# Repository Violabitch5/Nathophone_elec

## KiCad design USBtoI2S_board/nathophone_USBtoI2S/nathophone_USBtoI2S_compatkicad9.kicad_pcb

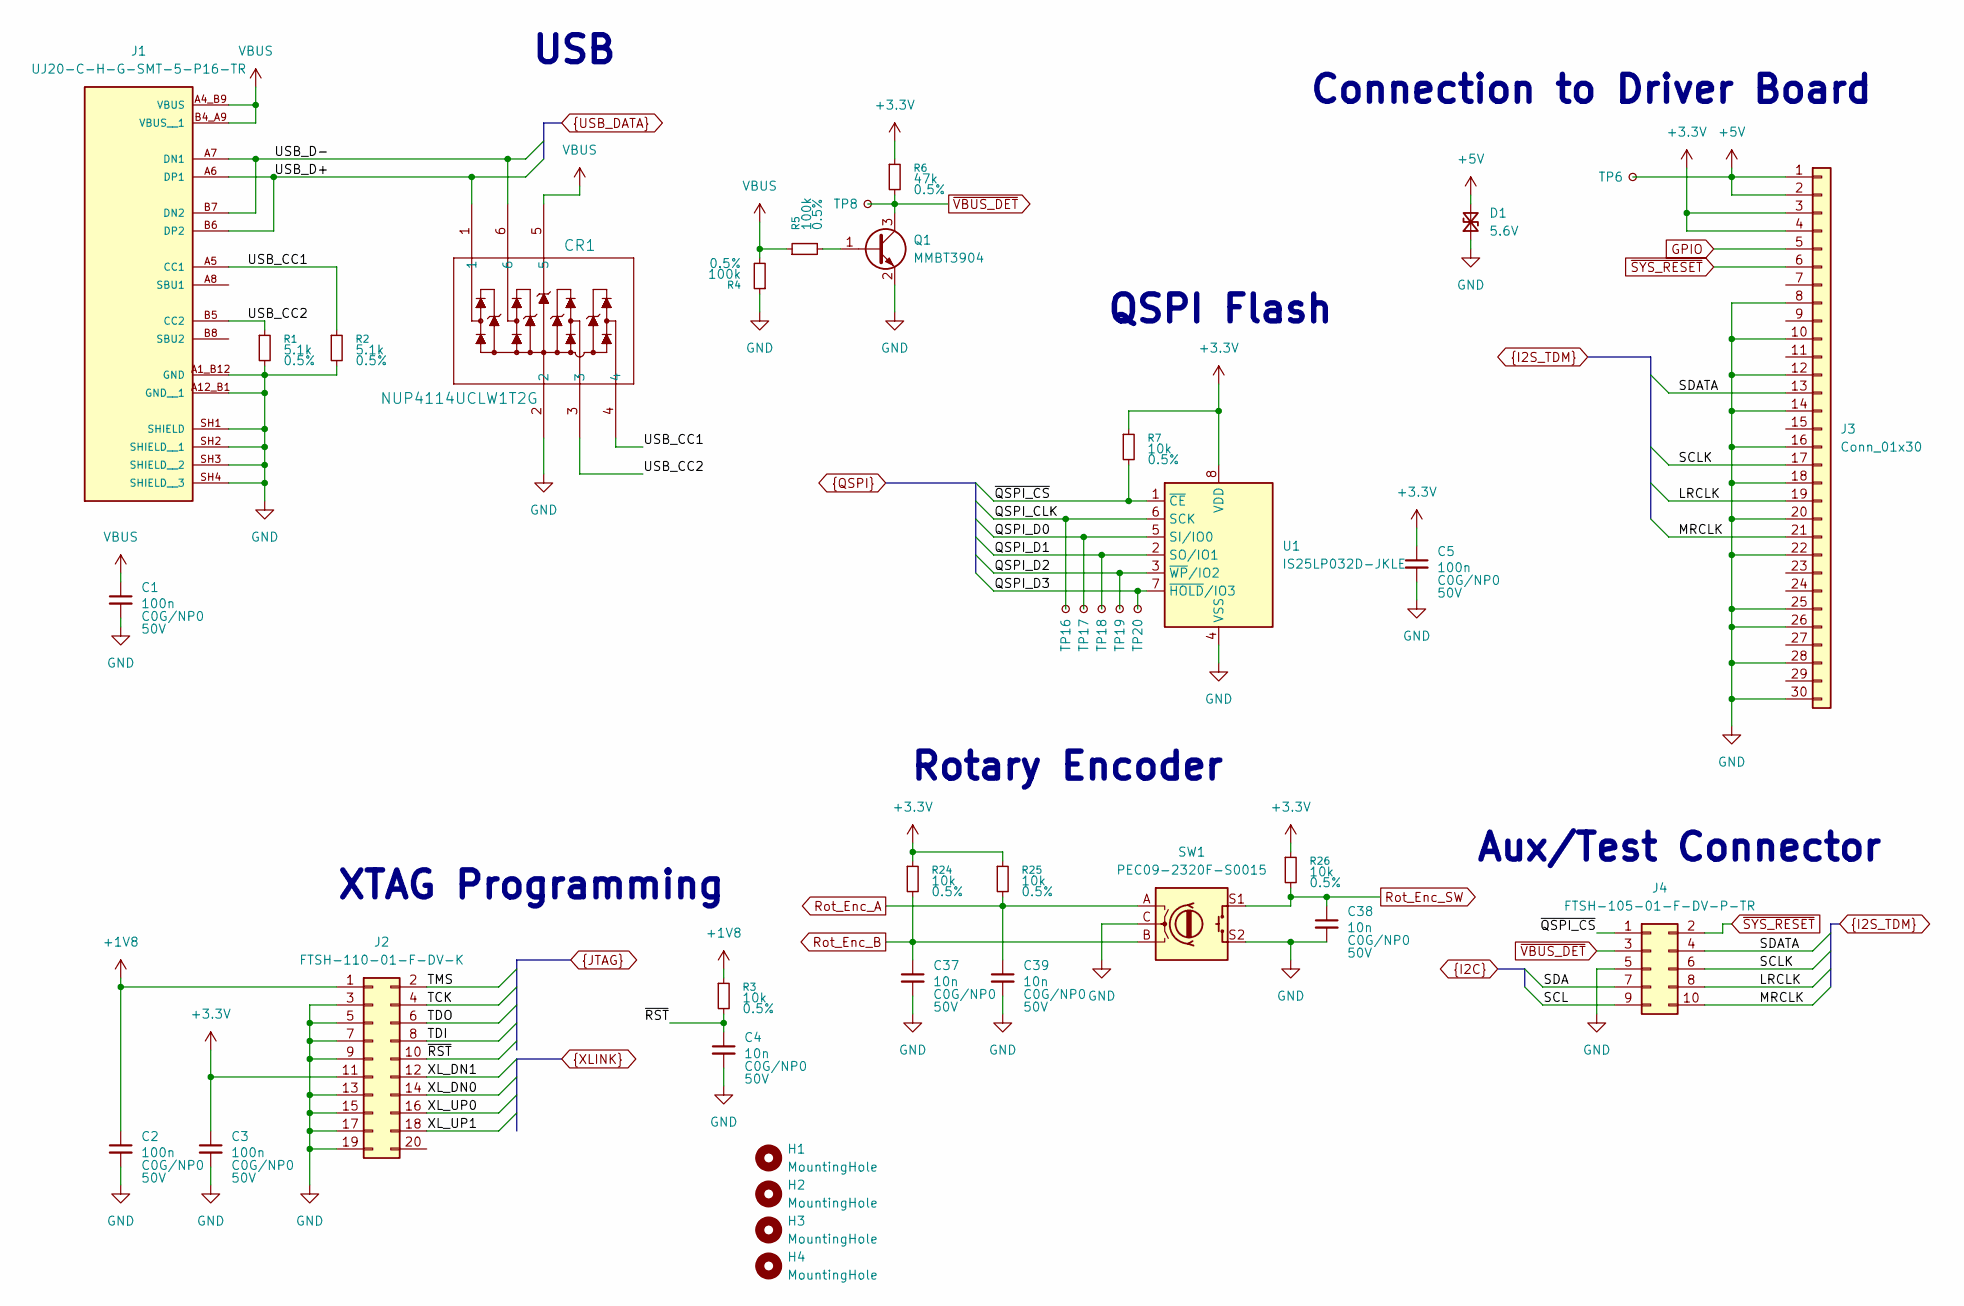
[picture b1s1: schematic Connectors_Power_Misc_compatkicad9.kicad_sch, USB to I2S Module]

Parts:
C1, C2, C3, C5: 100n; CAPC1810X65N; Voltage Rating 50V; MPN GRMJN65C1H104JE01D; DigiKey Part Number 490-GRMJN65C1H104JE01DCT-ND
C4, C37, C38, C39: 10n; C_0805_2012Metric_Pad1.18x1.45mm_HandSolder; Voltage Rating 50V; MPN GRM2195C1H103JA01D; DigiKey Part Number 490-1642-1-ND
CR1: NUP4114UCLW1T2G; SOT-363_SC-70-6; MPN NUP4114UCLW1T2G; DigiKey Part Number NUP4114UCLW1T2GOSCT-ND
D1: 5.6V; SOD-962_SL2_TOS; MPN DF2B6M4BSL,L3F; DigiKey Part Number 264-DF2B6M4BSL,L3FCT-ND
H1, H2, H3, H4: MountingHole; MountingHole_2.7mm_M2.5_DIN965
J1: UJ20-C-H-G-SMT-5-P16-TR; SAMESKY_UJ20-C-H-G-SMT-5-P16-TR; PARTREV 1.01; DigiKey Part Number 2223-UJ20-C-H-G-SMT-5-P16-TRCT-ND
J2: FTSH-110-01-F-DV-K; CON20_2X10_DUK_FTSH_SAI-M; MPN FTSH-110-01-F-DV-K; DigiKey Part Number SAM8802-ND
J3: Conn_01x30; CON_525593072_MOL; MPN 0525593072; DigiKey Part Number 900-0525593072TR-ND
J4: FTSH-105-01-F-DV-P-TR; PinHeader_2x05_P1.27mm_Vertical_SMD; MPN FTSH-105-01-F-DV-P-TR; DigiKey Part Number SAM13161CT-ND
Q1: MMBT3904; SOT-23; MPN MMBT3904; DigiKey Part Number 4530-MMBT3904CT-ND
R1, R2: 5.1k; R_0805_2012Metric_Pad1.20x1.40mm_HandSolder; MPN RNCF0805DTE5K10; DigiKey Part Number 738-RNCF0805DTE5K10CT-ND
R3, R7, R24, R25, R26: 10k; R_0805_2012Metric_Pad1.20x1.40mm_HandSolder; MPN RNCF0805DTE10K0; DigiKey Part Number RNCF0805DTE10K0CT-ND
R4, R5: 100k; R_0805_2012Metric_Pad1.20x1.40mm_HandSolder; MPN RNCF0805DTE100K; DigiKey Part Number 738-RNCF0805DTE100KCT-ND
R6: 47k; R_0805_2012Metric_Pad1.20x1.40mm_HandSolder; MPN RNCF0805DTE47K0; DigiKey Part Number 738-RNCF0805DTE47K0CT-ND
SW1: PEC09-2320F-S0015; RotaryEncoder_Bourns_Horizontal_PEC09-2xxxF-Sxxxx; MPN PEC09-2320F-S0015; DigiKey Part Number PEC09-2320F-S0015-ND
TP6, TP8, TP16, TP17, TP18, TP19, TP20: TestPoint_Small; TestPoint_Pad_D1.5mm
U1: IS25LP032D-JKLE; WSON-8-1EP_6x5mm_P1.27mm_EP3.4x4mm; MPN IS25LP032D-JKLE-TR; DigiKey Part Number 706-IS25LP032D-JKLE-TRCT-ND

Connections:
+1V8: C2.1, J2.1, R3.1; also elsewhere on the board
+3.3V: C3.1, C5.1, J2.11, J3.3, J3.4, R6.1, R7.1, R24.1, R25.1, R26.1, U1.8 (VDD); also elsewhere on the board
+5V: D1.2 (A2), J3.1, J3.2, TP6.1 (1_1); also elsewhere on the board
/Connectors_Misc/USB_CC1: CR1.4, J1.A5 (CC1), R2.1
/Connectors_Misc/USB_CC2: CR1.3, J1.B5 (CC2), R1.1
GND: C1.2, C2.2, C3.2, C4.2, C5.2, C37.2, C38.2, C39.2, CR1.2, D1.1 (A1), J1.A1_B12 (GND), J1.A12_B1 (GND__1), J1.SH1 (SHIELD), J1.SH2 (SHIELD__1), J1.SH3 (SHIELD__2), J1.SH4 (SHIELD__3), J2.3, J2.5, J2.7, J2.9, J2.13, J2.15, J2.17, J2.19, J3.8, J3.10, J3.12, J3.14, J3.16, J3.18, J3.20, J3.22, J3.25, J3.26, J3.28, J3.30, J4.5, Q1.2 (E), R1.2, R2.2, R4.1, SW1.C, SW1.S2, U1.4 (VSS); also elsewhere on the board
GPIO: J3.5; also elsewhere on the board
LRCLK: J3.19, J4.8; also elsewhere on the board
MRCLK: J3.21, J4.10; also elsewhere on the board
unnamed: Q1.1 (B), R5.2
QSPI_CLK: TP16.1 (1_1), U1.6 (SCK); also elsewhere on the board
QSPI_D0: TP17.1 (1_1), U1.5 (SI/IO0); also elsewhere on the board
QSPI_D1: TP18.1 (1_1), U1.2 (SO/IO1); also elsewhere on the board
QSPI_D2: TP19.1 (1_1), U1.3 (~WP/IO2); also elsewhere on the board
QSPI_D3: TP20.1 (1_1), U1.7 (~HOLD/IO3); also elsewhere on the board
Rot_Enc_A: C39.1, R25.2, SW1.A; also elsewhere on the board
Rot_Enc_B: C37.1, R24.2, SW1.B; also elsewhere on the board
Rot_Enc_SW: C38.1, R26.2, SW1.S1; also elsewhere on the board
SCL: J4.9; also elsewhere on the board
SCLK: J3.17, J4.6; also elsewhere on the board
SDA: J4.7; also elsewhere on the board
SDATA: J3.13, J4.4; also elsewhere on the board
TCK: J2.4; also elsewhere on the board
TDI: J2.8; also elsewhere on the board
TDO: J2.6; also elsewhere on the board
TMS: J2.2; also elsewhere on the board
USB_D+: CR1.1, J1.A6 (DP1), J1.B6 (DP2); also elsewhere on the board
USB_D-: CR1.6, J1.A7 (DN1), J1.B7 (DN2); also elsewhere on the board
VBUS: C1.1, CR1.5, J1.A4_B9 (VBUS), J1.B4_A9 (VBUS__1), R4.2, R5.1
XL_DN0: J2.14; also elsewhere on the board
XL_DN1: J2.12; also elsewhere on the board
XL_UP0: J2.16; also elsewhere on the board
XL_UP1: J2.18; also elsewhere on the board
~QSPI_CS: J4.1, R7.2, U1.1 (~CE); also elsewhere on the board
~RST: C4.1, J2.10, R3.2; also elsewhere on the board
~SYS_RESET: J3.6, J4.2; also elsewhere on the board
~VBUS_DET: J4.3, Q1.3 (C), R6.2, TP8.1 (1_1); also elsewhere on the board

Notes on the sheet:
Connection to Driver Board
Rotary Encoder
USB
QSPI Flash
XTAG Programming
Aux/Test Connector

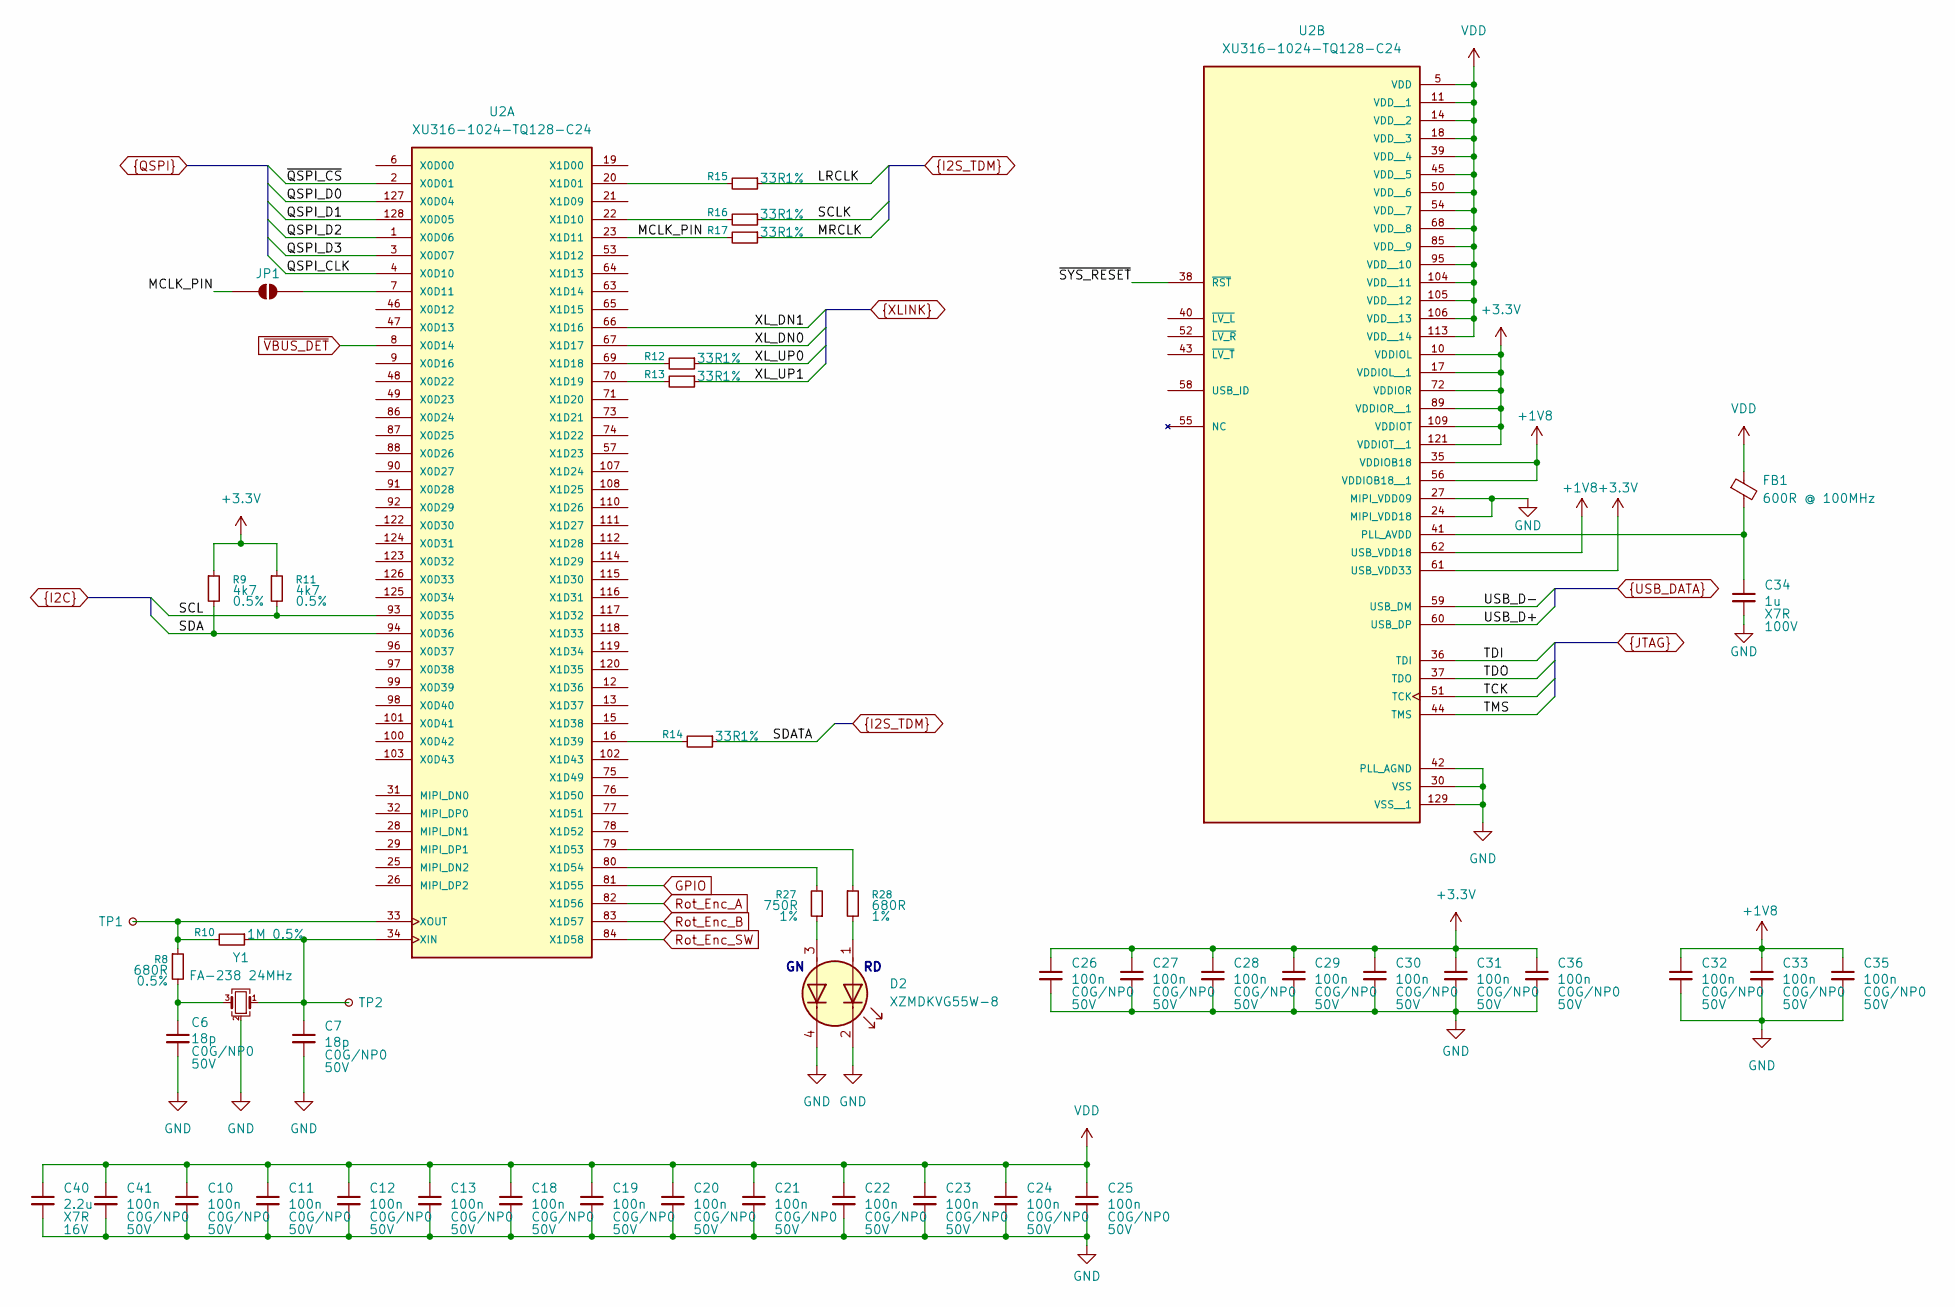
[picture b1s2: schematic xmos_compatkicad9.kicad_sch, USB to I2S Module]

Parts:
C6, C7: 18p; C_0603_1608Metric; Voltage Rating 50V; MPN C0603C180C5GACTU; DigiKey Part Number 399-C0603C180C5GACTUCT-ND
C10, C11, C12, C13, C18, C19, C20, C21, C22, C23, C24, C25, C26, C27, C28, C29, C30, C31, C32, C33, C35, C36, C41: 100n; CAPC1810X65N; Voltage Rating 50V; MPN GRMJN65C1H104JE01D; DigiKey Part Number 490-GRMJN65C1H104JE01DCT-ND
C34: 1u; C_0603_1608Metric; Voltage Rating 100V; MPN C1608X7R2A105K080AC; DigiKey Part Number 445-C1608X7R2A105K080ACCT-ND
C40: 2.2u; C_0805_2012Metric_Pad1.18x1.45mm_HandSolder; Voltage Rating 16V; MPN C2012X7R1C225K125AB; DigiKey Part Number 445-1420-1-ND
D2: XZMDKVG55W-8; LED_XZMDKVG55W-8; MPN XZMDKVG55W-8; DigiKey Part Number 1497-1183-1-ND
FB1: 600R @ 100MHz; C_0805_2012Metric_Pad1.18x1.45mm_HandSolder; MPN HZ0805E601R-10; DigiKey Part Number 240-2399-1-ND
JP1: SolderJumper_2_Open; SolderJumper-2_P1.3mm_Open_RoundedPad1.0x1.5mm
R8: 680R; R_0603_1608Metric; MPN RT0603DRD07680RL; DigiKey Part Number 311-680DCT-ND
R9, R11: 4k7; R_0805_2012Metric_Pad1.20x1.40mm_HandSolder; MPN RNCF0805DTE4K70; DigiKey Part Number 738-RNCF0805DTE4K70CT-ND
R10: 1M; R_0603_1608Metric; MPN RC0603DR-071ML; DigiKey Part Number 13-RC0603DR-071MLCT-ND
R12, R13, R14, R15, R16, R17: 33R; R_0805_2012Metric_Pad1.20x1.40mm_HandSolder; MPN RC0805FR-0733RL; DigiKey Part Number 311-33.0CRCT-ND
R27: 750R; R_0805_2012Metric_Pad1.20x1.40mm_HandSolder; MPN CRCW0805750RFKEA; DigiKey Part Number 541-750CCT-ND
R28: 680R; R_0805_2012Metric_Pad1.20x1.40mm_HandSolder; MPN CRCW0805680RFKEA; DigiKey Part Number 541-680CCT-ND
TP1, TP2: TestPoint_Small; TestPoint_Pad_D1.5mm
U2: XU316-1024-TQ128-C24; QFP40P1600X1600X120-129N; PARTREV 2025/1/13; DigiKey Part Number 880-XU316-1024-TQ128-C24-ND
Y1: FA-238 24MHz; Crystal_SMD_3225-4Pin_3.2x2.5mm; MPN FA-238 24.0000MB-C3; DigiKey Part Number SER3689CT-ND

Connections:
+1V8: C32.1, C33.1, C35.1, U2.35 (VDDIOB18), U2.56 (VDDIOB18__1), U2.62 (USB_VDD18); also elsewhere on the board
+3.3V: C26.1, C27.1, C28.1, C29.1, C30.1, C31.1, C36.1, R9.1, R11.1, U2.10 (VDDIOL), U2.17 (VDDIOL__1), U2.61 (USB_VDD33), U2.72 (VDDIOR), U2.89 (VDDIOR__1), U2.109 (VDDIOT), U2.121 (VDDIOT__1); also elsewhere on the board
/XMOS/MCLK_PIN: JP1.2 (B), R17.2, U2.23 (X1D11)
/XMOS/~SYS_RESET: U2.38 (~RST)
GND: C6.2, C7.2, C10.2, C11.2, C12.2, C13.2, C18.2, C19.2, C20.2, C21.2, C22.2, C23.2, C24.2, C25.2, C26.2, C27.2, C28.2, C29.2, C30.2, C31.2, C32.2, C33.2, C34.2, C35.2, C36.2, C40.2, C41.2, D2.2 (K1), D2.4 (K2), U2.24 (MIPI_VDD18), U2.27 (MIPI_VDD09), U2.30 (VSS), U2.42 (PLL_AGND), U2.129 (VSS__1), Y1.2 (G), Y1.4 (G); also elsewhere on the board
GPIO: U2.81 (X1D55); also elsewhere on the board
LRCLK: R15.1; also elsewhere on the board
MRCLK: R17.1; also elsewhere on the board
unnamed: C6.1, R8.2, Y1.3
unnamed: D2.1 (A1), R28.2
unnamed: D2.3 (A2), R27.1
unnamed: JP1.1 (A), U2.7 (X0D11)
unnamed: R15.2, U2.20 (X1D01)
unnamed: R16.2, U2.22 (X1D10)
unnamed: R12.2, U2.69 (X1D18)
unnamed: R13.2, U2.70 (X1D19)
unnamed: R14.2, U2.16 (X1D39)
unnamed: R28.1, U2.79 (X1D53)
unnamed: R27.2, U2.80 (X1D54)
unnamed: C7.1, R10.1, TP2.1 (1_1), U2.34 (XIN), Y1.1
unnamed: R8.1, R10.2, TP1.1 (1_1), U2.33 (XOUT)
unnamed: C34.1, FB1.2, U2.41 (PLL_AVDD)
QSPI_CLK: U2.4 (X0D10); also elsewhere on the board
QSPI_D0: U2.127 (X0D04); also elsewhere on the board
QSPI_D1: U2.128 (X0D05); also elsewhere on the board
QSPI_D2: U2.1 (X0D06); also elsewhere on the board
QSPI_D3: U2.3 (X0D07); also elsewhere on the board
Rot_Enc_A: U2.82 (X1D56); also elsewhere on the board
Rot_Enc_B: U2.83 (X1D57); also elsewhere on the board
Rot_Enc_SW: U2.84 (X1D58); also elsewhere on the board
SCL: R11.2, U2.93 (X0D35); also elsewhere on the board
SCLK: R16.1; also elsewhere on the board
SDA: R9.2, U2.94 (X0D36); also elsewhere on the board
SDATA: R14.1; also elsewhere on the board
TCK: U2.51 (TCK); also elsewhere on the board
TDI: U2.36 (TDI); also elsewhere on the board
TDO: U2.37 (TDO); also elsewhere on the board
TMS: U2.44 (TMS); also elsewhere on the board
USB_D+: U2.60 (USB_DP); also elsewhere on the board
USB_D-: U2.59 (USB_DM); also elsewhere on the board
VDD: C10.1, C11.1, C12.1, C13.1, C18.1, C19.1, C20.1, C21.1, C22.1, C23.1, C24.1, C25.1, C40.1, C41.1, FB1.1, U2.5 (VDD), U2.11 (VDD__1), U2.14 (VDD__2), U2.18 (VDD__3), U2.39 (VDD__4), U2.45 (VDD__5), U2.50 (VDD__6), U2.54 (VDD__7), U2.68 (VDD__8), U2.85 (VDD__9), U2.95 (VDD__10), U2.104 (VDD__11), U2.105 (VDD__12), U2.106 (VDD__13), U2.113 (VDD__14); also elsewhere on the board
XL_DN0: U2.67 (X1D17); also elsewhere on the board
XL_DN1: U2.66 (X1D16); also elsewhere on the board
XL_UP0: R12.1; also elsewhere on the board
XL_UP1: R13.1; also elsewhere on the board
~QSPI_CS: U2.2 (X0D01); also elsewhere on the board
~VBUS_DET: U2.8 (X0D14); also elsewhere on the board

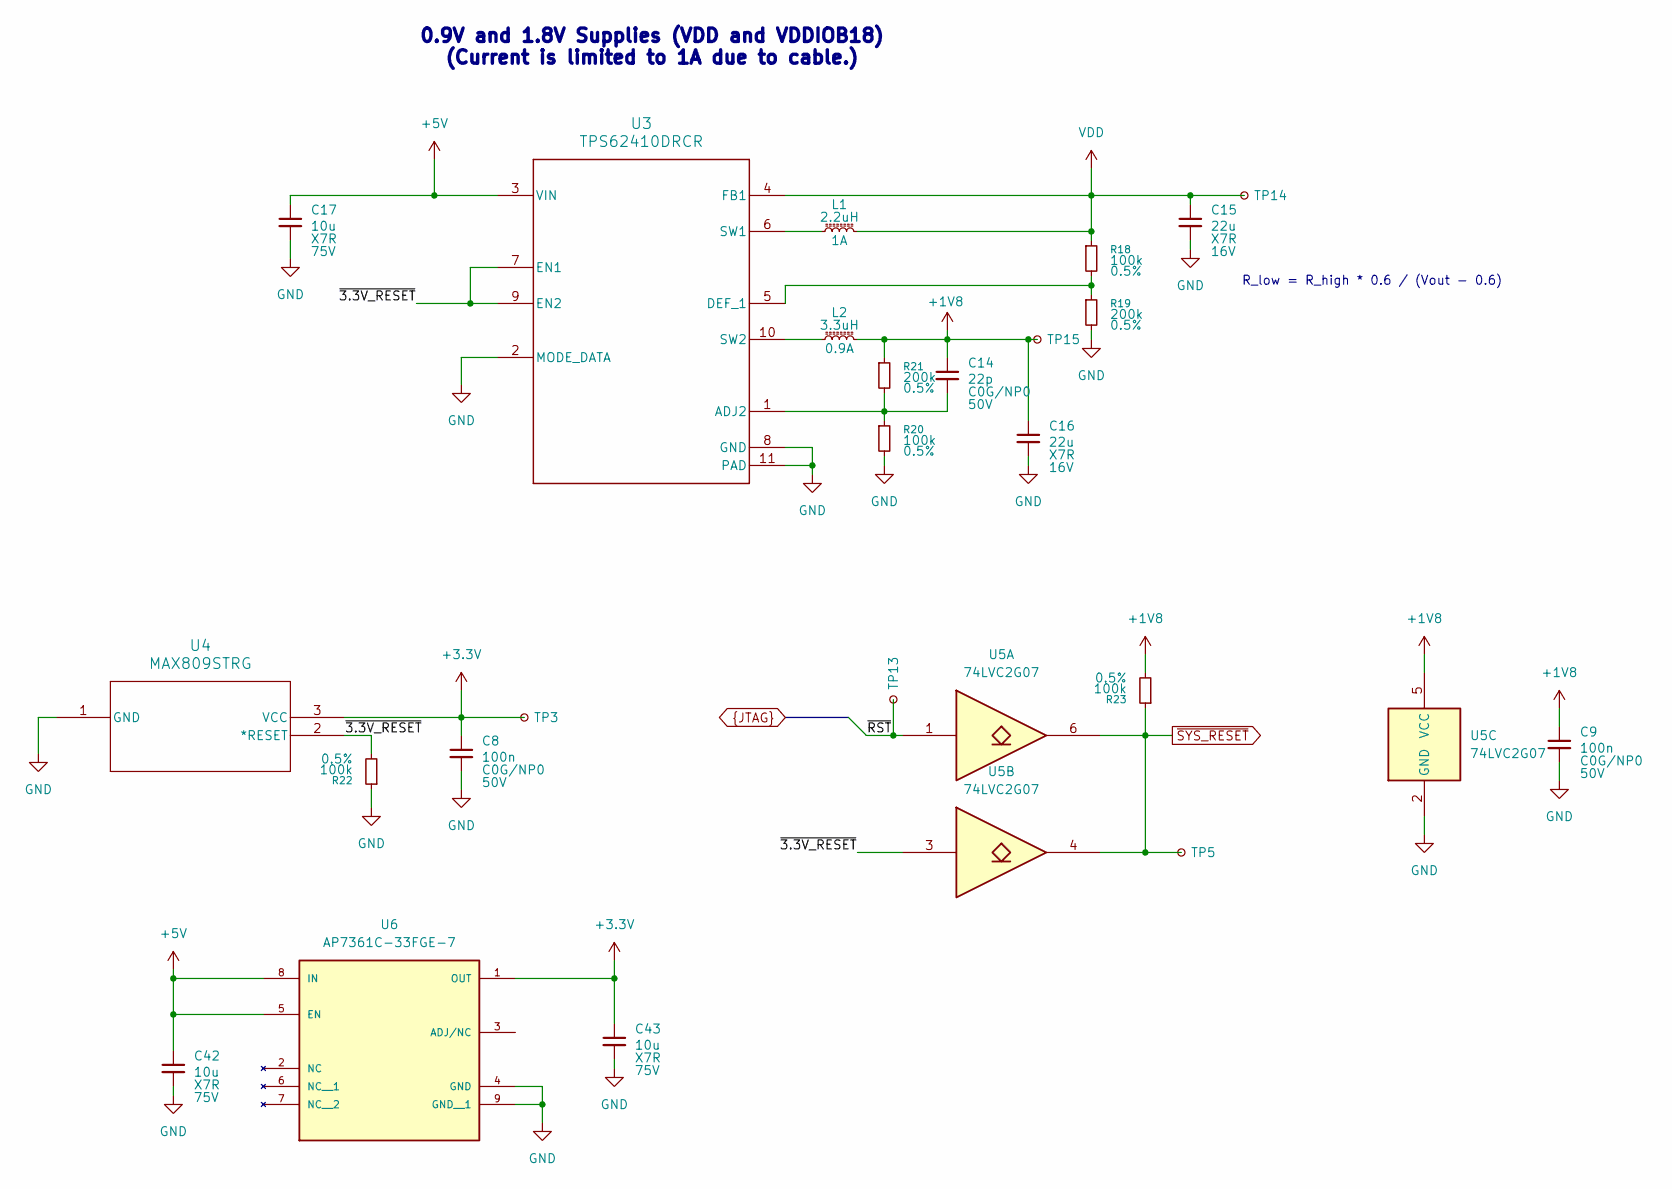
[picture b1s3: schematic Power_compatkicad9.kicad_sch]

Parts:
C8, C9: 100n; CAPC1810X65N; Voltage Rating 50V; MPN GRMJN65C1H104JE01D; DigiKey Part Number 490-GRMJN65C1H104JE01DCT-ND
C14: 22p; C_0603_1608Metric_Pad1.08x0.95mm_HandSolder; Voltage Rating 50V; MPN C0603C220J5GACTU; DigiKey Part Number 399-C0603C220J5GACTUCT-ND
C15, C16: 22u; C_1210_3225Metric_Pad1.33x2.70mm_HandSolder; Voltage Rating 16V; MPN CL32B226MOJNNNE; DigiKey Part Number 1276-3395-1-ND
C17, C42, C43: 10u; C_1210_3225Metric_Pad1.33x2.70mm_HandSolder; Voltage Rating 75V; MPN C3225X7R1N106K250AC; DigiKey Part Number 445-C3225X7R1N106K250ACCT-ND
L1: 2.2uH; IND_EPCOS_B82432T_EPC; MPN B82432T1222K000; DigiKey Part Number 495-1757-1-ND
L2: 3.3uH; IND_EPCOS_B82432T_EPC; MPN B82432T1332K000; DigiKey Part Number 495-1760-1-ND
R18, R20, R22, R23: 100k; R_0805_2012Metric_Pad1.20x1.40mm_HandSolder; MPN RNCF0805DTE100K; DigiKey Part Number 738-RNCF0805DTE100KCT-ND
R19, R21: 200k; R_0805_2012Metric_Pad1.20x1.40mm_HandSolder; MPN RNCF0805DTE200K; DigiKey Part Number 738-RNCF0805DTE200KCT-ND
TP3, TP5, TP13, TP14, TP15: TestPoint_Small; TestPoint_Pad_D1.5mm
U3: TPS62410DRCR; MPN TPS62410DRCR; DigiKey Part Number 296-25488-1-ND
U4: MAX809STRG; SOT-23; MPN MAX809STRG; DigiKey Part Number MAX809STRGOSCT-ND
U5: 74LVC2G07; SOT-363_SC-70-6; MPN 74LVC2G07GW,125; DigiKey Part Number 1727-4121-1-ND
U6: AP7361C-33FGE-7; SON65P300X300X63-9N; PARTREV 5 - 2; DigiKey Part Number AP7361C-33FGE-7DICT-ND

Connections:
+1V8: C9.1, C14.1, C16.1, L2.2, R21.1, R23.2, TP15.1 (1_1), U5.5 (VCC); also elsewhere on the board
+3.3V: C8.1, C43.1, TP3.1 (1_1), U4.3 (VCC), U6.1 (OUT); also elsewhere on the board
+5V: C17.1, C42.1, U3.3 (VIN), U6.5 (EN), U6.8 (IN); also elsewhere on the board
/Power/~3.3V_RESET: R22.2, U3.7 (EN1), U3.9 (EN2), U4.2 (*RESET), U5.3
GND: C8.2, C9.2, C15.2, C16.2, C17.2, C42.2, C43.2, R19.2, R20.2, R22.1, U3.2 (MODE_DATA), U3.8 (GND), U3.11 (PAD), U4.1 (GND), U5.2 (GND), U6.4 (GND), U6.9 (GND__1); also elsewhere on the board
unnamed: C14.2, R20.1, R21.2, U3.1 (ADJ2)
unnamed: R18.2, R19.1, U3.5 (DEF_1)
unnamed: L1.1, U3.6 (SW1)
unnamed: L2.1, U3.10 (SW2)
VDD: C15.1, L1.2, R18.1, TP14.1 (1_1), U3.4 (FB1); also elsewhere on the board
~RST: TP13.1 (1_1), U5.1; also elsewhere on the board
~SYS_RESET: R23.1, TP5.1 (1_1), U5.4, U5.6; also elsewhere on the board

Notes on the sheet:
R_low = R_high * 0.6 / (Vout - 0.6)
0.9V and 1.8V Supplies (VDD and VDDIOB18) (Current is limited to 1A due to cable.)

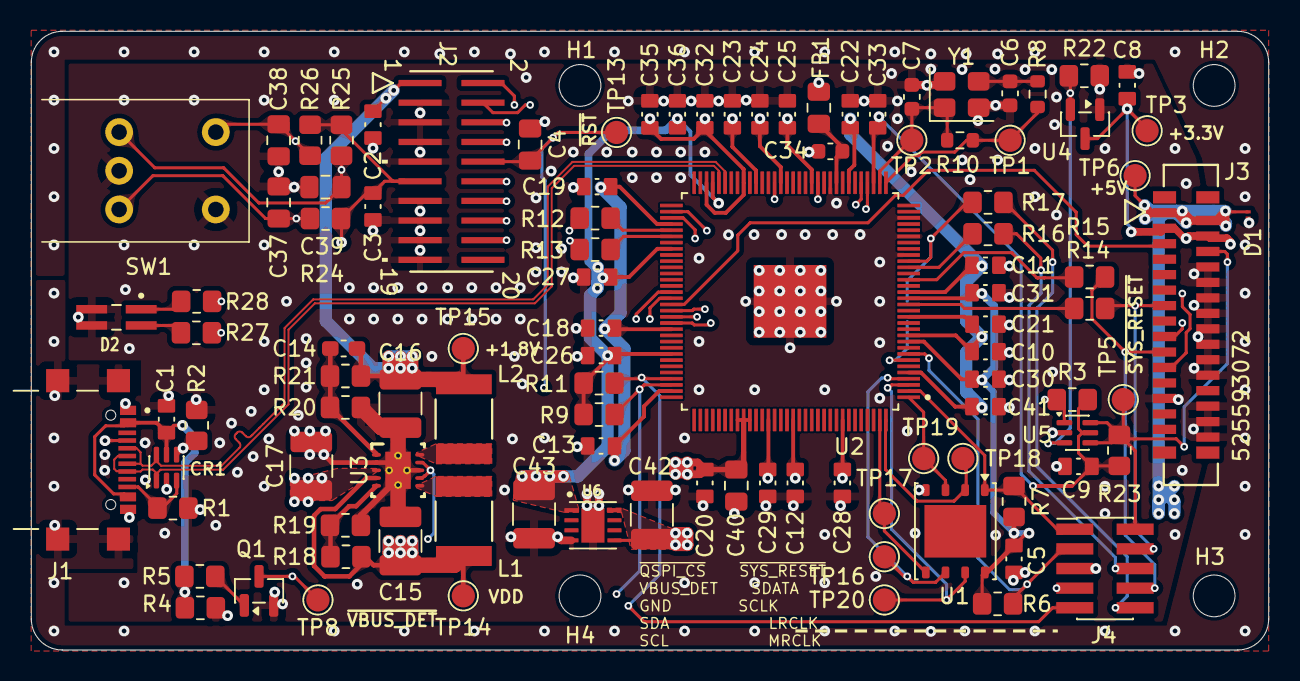
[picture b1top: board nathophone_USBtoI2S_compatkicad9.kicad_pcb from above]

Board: 4 copper layers, 80.0 x 40.0 mm, 109 parts (1 on the bottom side), 58 nets.

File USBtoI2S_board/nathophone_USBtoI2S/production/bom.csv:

Designator,Footprint,Quantity,Value,LCSC Part #
"C1, C10, C11, C12, C13, C18, C19, C2, C20, C21, C22, C23, C24, C25, C26, C27, C28, C29, C3, C30, C31, C32, C33, C35, C36, C41, C5, C8, C9",CAPC1810X65N,29,100n,GRMJN65C1H104JE01D
C14,0603,1,22p,C0603C220J5GACTU
"C15, C16",1210,2,22u,CL32B226MOJNNNE
C17,1210,1,10u,C3225X7R1N106K250AC
C34,0603,1,1u,C1608X7R2A105K080AC
"C37, C38, C39, C4",0805,4,10n,GRM2195C1H103JA01D
C40,0805,1,2.2u,C2012X7R1C225K125AB
"C6, C7",0603,2,18p,C0603C180C5GACTU
CR1,SOT-363_SC-70-6,1,NUP4114UCLW1T2G,NUP4114UCLW1T2G
D2,LED_XZMDKVG55W-8,1,XZMDKVG55W-8,XZMDKVG55W-8
FB1,0805,1,600R @ 100MHz,HZ0805E601R-10
J1,SAMESKY_UJ20-C-H-G-SMT-5-P16-TR,1,UJ20-C-H-G-SMT-5-P16-TR,UJ20-C-H-G-SMT-5-P16-TR
J2,CON20_2X10_DUK_FTSH_SAI-M,1,FTSH-110-01-F-DV-K,FTSH-110-01-F-DV-K
J3,CON_525593072_MOL,1,Conn_01x30,0525593072
J4,PinHeader_2x05_P1.27mm_Vertical_SMD,1,FTSH-105-01-F-DV-P-TR,FTSH-105-01-F-DV-P-TR
L1,IND_EPCOS_B82432T_EPC,1,2.2uH,B82432T1222K000
L2,IND_EPCOS_B82432T_EPC,1,3.3uH,B82432T1332K000
Q1,SOT-23,1,MMBT3904,MMBT3904
"R1, R2",0805,2,5.1k,RNCF0805DTE5K10
R10,0603,1,1M,RC0603DR-071ML
"R11, R9",0805,2,4k7,RNCF0805DTE4K70
"R12, R13, R14, R15, R16, R17",0805,6,33R,RC0805FR-0733RL
"R18, R20, R22, R23, R4, R5",0805,6,100k,RNCF0805DTE100K
"R19, R21",0805,2,200k,RNCF0805DTE200K
"R24, R25, R26, R3, R7",0805,5,10k,RNCF0805DTE10K0
R27,0805,1,750R,CRCW0805750RFKEA
R28,0805,1,680R,CRCW0805680RFKEA
R6,0805,1,47k,RNCF0805DTE47K0
R8,0603,1,680R,RT0603DRD07680RL
SW1,RotaryEncoder_Bourns_Horizontal_PEC09-2xxxF-Sxxxx,1,PEC09-2320F-S0015,PEC09-2320F-S0015
"TP1, TP13, TP14, TP15, TP16, TP17, TP18, TP19, TP2, TP20, TP3, TP5, TP6, TP8",TestPoint_Pad_D1.5mm,14,TestPoint_Small,
U1,WSON-8-1EP_6x5mm_P1.27mm_EP3.4x4mm,1,IS25LP032D-JKLE,IS25LP032D-JKLE-TR
U2,QFP40P1600X1600X120-129N,1,XU316-1024-TQ128-C24,XU316-1024-TQ128-C24
U3,TPS62410DRCR,1,TPS62410DRCR,TPS62410DRCR
U4,SOT-23,1,MAX809STRG,MAX809STRG
U5,SOT-363_SC-70-6,1,74LVC2G07,"74LVC2G07GW,125"
Y1,Crystal_SMD_3225-4Pin_3.2x2.5mm,1,FA-238 24MHz,FA-238 24.0000MB-C3

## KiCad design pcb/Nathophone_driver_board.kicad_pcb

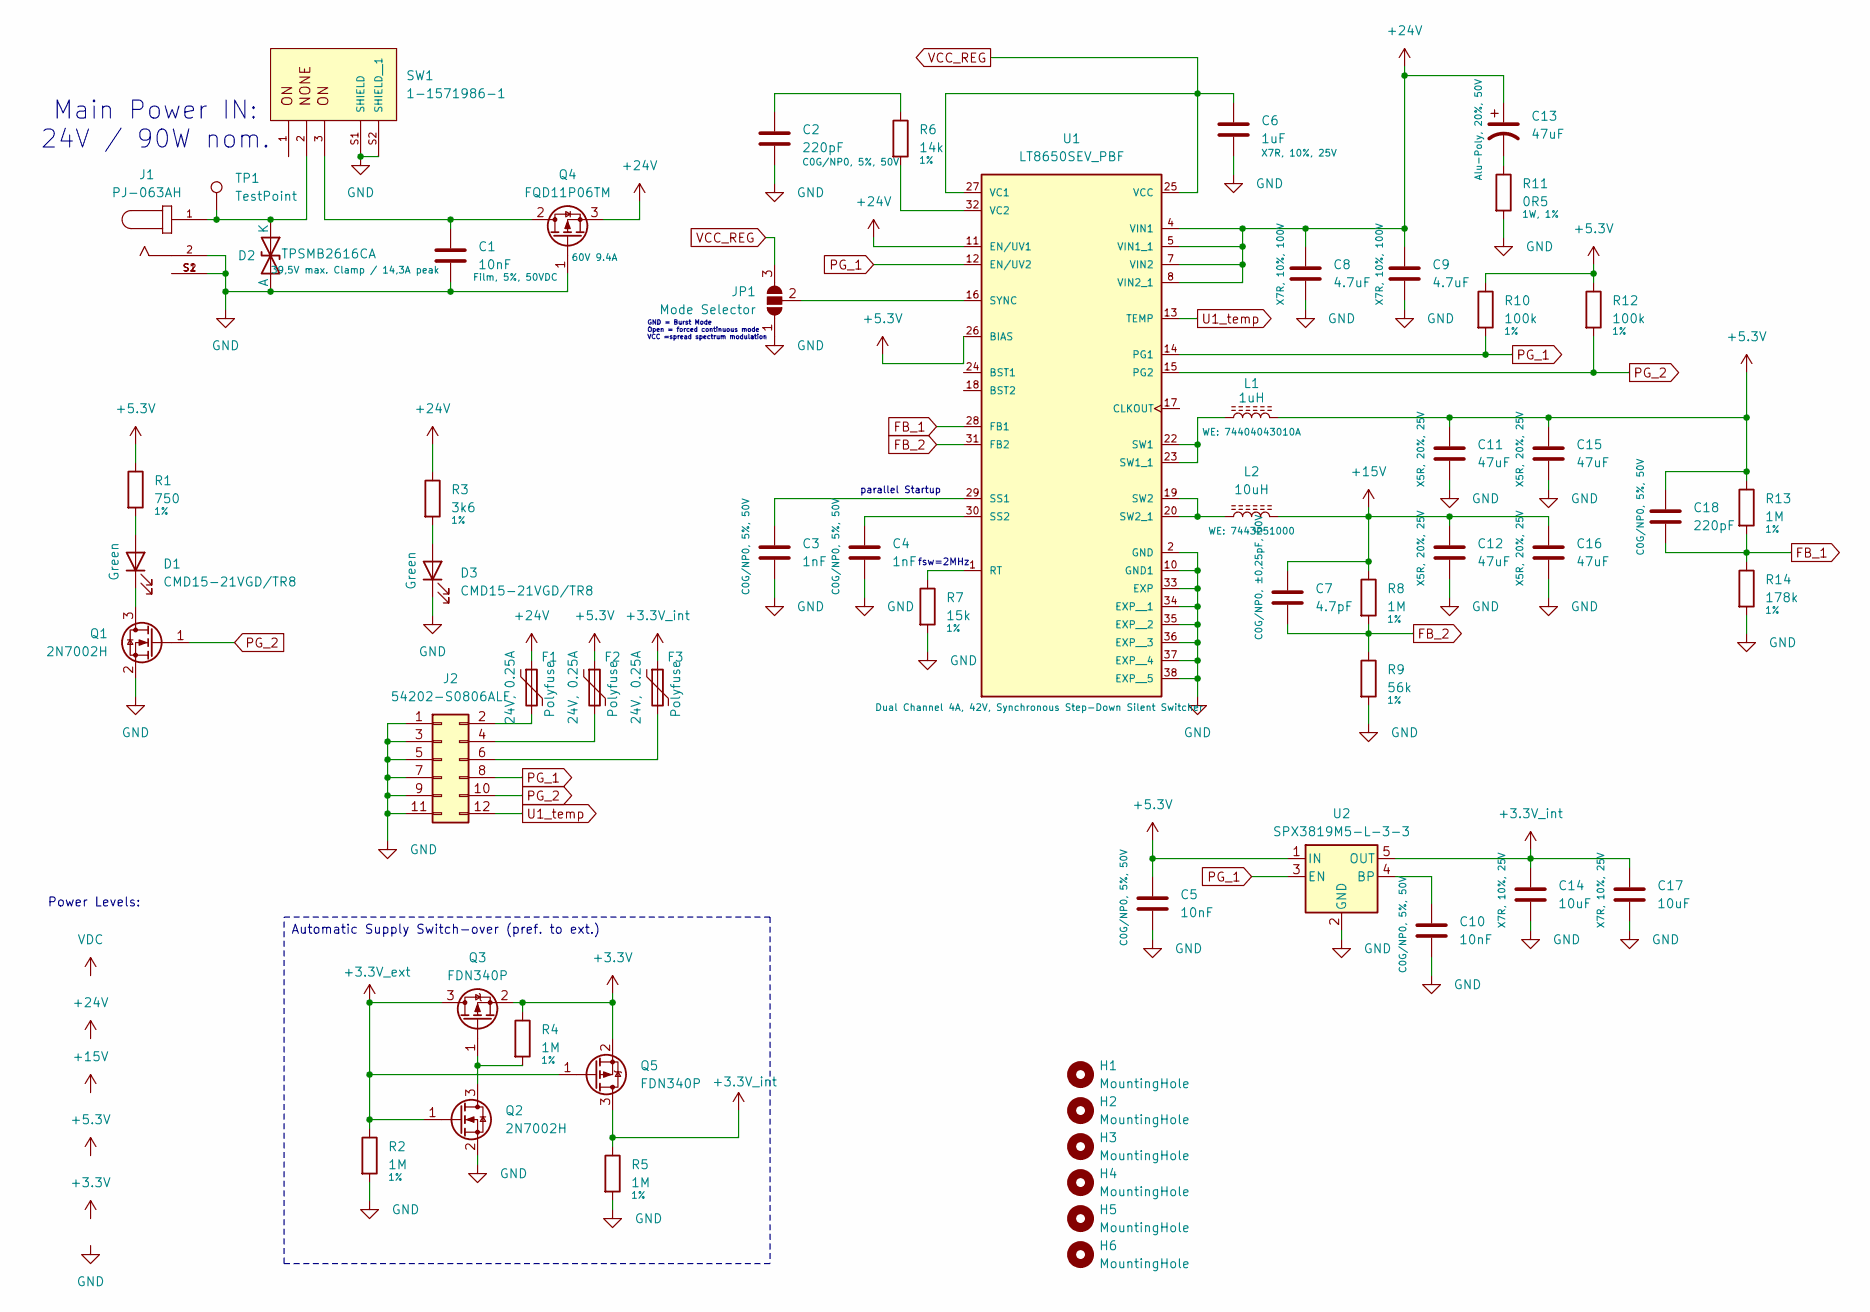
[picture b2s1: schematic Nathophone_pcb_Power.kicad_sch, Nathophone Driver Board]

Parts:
C1: 10nF; C_1206_3216Metric; MPN ECH-U1H103JX5; DigiKey_PartNo PCF1340TR-ND
C2, C18: 220pF; C_0805_2012Metric; MPN CL21C221JBANNNC; DigiKey_PartNo 1276-1164-2-ND
C3, C4: 1nF; C_0805_2012Metric; MPN CL21C102JBCNFNC; DigiKey_PartNo 1276-2576-2-ND
C5, C10: 10nF; C_0805_2012Metric; MPN CL21C103JBF1PNE; DigiKey_PartNo 1276-6790-2-ND
C6: 1uF; C_0805_2012Metric; MPN CL21B105KAFNNNE; DigiKey_PartNo 1276-1066-2-ND
C7: 4.7pF; C_0402_1005Metric; MPN CL05C4R7CB51PNC; DigiKey_PartNo 1276-6694-2-ND
C8, C9: 4.7uF; C_1206_3216Metric; MPN C3216X7R2A475K160AC; DigiKey_PartNo 445-C3216X7R2A475K160ACTR-ND
C11, C12, C15, C16: 47uF; C_1206_3216Metric; MPN C3216X5R1E476M160AC; DigiKey_PartNo 445-8047-2-ND
C13: 47uF; CP_Elec_8x10; MPN GXC1H470MCQ1GS; DigiKey_PartNo GXC1H470MCQ1GTR-ND
C14, C17: 10uF; C_1206_3216Metric; MPN CL31B106KAHNNNE; DigiKey_PartNo 1276-1804-2-ND
D1, D3: CMD15-21VGD/TR8; LED_1206_3216Metric; MPN CMD15-21VGD/TR8; DigiKey_PartNo L62305TR-ND
D2: TPSMB2616CA; D_SMB; MPN TPSMB2616CA; DigiKey_PartNo 18-TPSMB2616CATR-ND
F1, F2, F3: Polyfuse; Fuse_1206_3216Metric; MPN 0ZCJ0025AF2E; DigiKey_PartNo 5923-0ZCJ0025AF2ETR-ND
H1, H2, H3, H4, H5, H6: MountingHole; MountingHole_3.2mm_M3
J1: PJ-063AH; CUI_PJ-063AH; PARTREV 1.02; DigiKey_PartNo CP-063AH-ND
J2: 54202-S0806ALF; PinHeader_2x06_P2.54mm_Vertical_SMD; MPN 54202-S0806ALF; DigiKey_PartNo 609-54202-S0806ALFTR-ND
JP1: Mode Selector; SolderJumper-3_P1.3mm_Open_RoundedPad1.0x1.5mm
L1: 1uH; WE-LQS_4025; MPN 74404043010A; DigiKey_PartNo 732-10753-2-ND
L2: 10uH; WE-HCI_1050; MPN 7443251000; DigiKey_PartNo 732-4179-2-ND
Q1, Q2: 2N7002H; SOT-23; MPN 2N7002H-7; DigiKey_PartNo 2N7002H-7DITR-ND
Q3, Q5: FDN340P; SOT-23; MPN FDN340P; DigiKey_PartNo FDN340PTR-ND
Q4: FQD11P06TM; TO-252-2; MPN FQD11P06TM; DigiKey_PartNo FQD11P06TMTR-ND
R1: 750; R_0805_2012Metric; MPN CRCW0805750RFKEA; DigiKey_PartNo 541-750CTR-ND
R2, R4, R5, R8, R13: 1M; R_0805_2012Metric; MPN CRCW08051M00FKEA; DigiKey_PartNo 541-1.00MCTR-ND
R3: 3k6; R_0805_2012Metric; MPN CRCW08053K60FKEA; DigiKey_PartNo 541-3.60KCTR-ND
R6: 14k; R_0805_2012Metric; MPN CRCW080514K0FKEA; DigiKey_PartNo 541-14.0KCTR-ND
R7: 15k; R_0805_2012Metric; MPN CRCW080515K0FKEA; DigiKey_PartNo 541-15.0KCTR-ND
R9: 56k; R_0805_2012Metric; MPN CRCW080556K0FKEA; DigiKey_PartNo 541-56.0KCTR-ND
R10, R12: 100k; R_0805_2012Metric; MPN CRCW0805100KFKEA; DigiKey_PartNo 541-100KCTR-ND
R11: 0R5; R_1206_3216Metric; MPN MFHA1206R5000FC; DigiKey_PartNo 283-MFHA1206R5000FCTR-ND
R14: 178k; R_0805_2012Metric; MPN CRCW0805178KFKEA; DigiKey_PartNo 541-178KCTR-ND
SW1: 1-1571986-1; TE_1-1571986-1; PARTREV A12; DigiKey_PartNo 450-1518-ND
TP1: TestPoint; TestPoint_Pad_D2.0mm
U1: LT8650SEV_PBF; QFN50P600X400X103-32N240X440; MPN LT8650SEV#PBF; DigiKey_PartNo 505-LT8650SEV#PBF-ND
U2: SPX3819M5-L-3-3; SOT-23-5; MPN SPX3819M5-L-3-3/TR; DigiKey_PartNo 1016-1873-2-ND

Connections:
+3.3V: Q3.2 (S), Q5.2 (S), R4.1; also elsewhere on the board
+3.3V_ext: Q2.1 (G), Q3.3 (D), Q5.1 (G), R2.1; also elsewhere on the board
+3.3V_int: C14.1, C17.1, F3.1, Q5.3 (D), R5.1, U2.5 (OUT); also elsewhere on the board
+5.3V: C5.1, C11.1, C15.1, C18.1, F2.1, L1.2, R1.1, R10.1, R12.1, R13.1, U1.26 (BIAS), U2.1 (IN); also elsewhere on the board
+15V: C7.1, C12.1, C16.1, L2.2, R8.1; also elsewhere on the board
+24V: C8.1, C9.1, C13.1, F1.1, Q4.3 (S), R3.1, U1.4 (VIN1), U1.5 (VIN1_1), U1.7 (VIN2), U1.8 (VIN2_1), U1.11 (EN/UV1)
FB_1: C18.2, R13.2, R14.1, U1.28 (FB1)
FB_2: C7.2, R8.2, R9.1, U1.31 (FB2)
GND: C1.2, C2.2, C3.2, C4.2, C5.2, C6.2, C8.2, C9.2, C10.2, C11.2, C12.2, C14.2, C15.2, C16.2, C17.2, D2.2 (A), D3.1 (K), J1.2, J1.S1 (SHIELD), J1.S2 (SHIELD__1), J2.1, J2.3, J2.5, J2.7, J2.9, J2.11, JP1.1 (A), Q1.2 (S), Q2.2 (S), Q4.1 (G), R2.2, R5.2, R7.2, R9.2, R11.2, R14.2, SW1.S1 (SHIELD), SW1.S2 (SHIELD__1), U1.2 (GND), U1.10 (GND1), U1.33 (EXP), U1.34 (EXP__1), U1.35 (EXP__2), U1.36 (EXP__3), U1.37 (EXP__4), U1.38 (EXP__5), U2.2 (GND); also elsewhere on the board
unnamed: C2.1, R6.1
unnamed: C13.2, R11.1
unnamed: D1.2 (A), R1.2
unnamed: D1.1 (K), Q1.3 (D)
unnamed: D2.1 (K), J1.1, SW1.2, TP1.1
unnamed: D3.2 (A), R3.2
unnamed: F1.2, J2.2
unnamed: F2.2, J2.4
unnamed: F3.2, J2.6
unnamed: JP1.2 (C), U1.16 (SYNC)
unnamed: Q2.3 (D), Q3.1 (G), R4.2
unnamed: C1.1, Q4.2 (D), SW1.3
unnamed: R7.1, U1.1 (RT)
unnamed: C3.1, U1.29 (SS1)
unnamed: C4.1, U1.30 (SS2)
unnamed: L1.1, U1.22 (SW1), U1.23 (SW1_1)
unnamed: L2.1, U1.19 (SW2), U1.20 (SW2_1)
unnamed: R6.2, U1.32 (VC2)
unnamed: C10.1, U2.4 (BP)
PG_1: J2.8, R10.2, U1.12 (EN/UV2), U1.14 (PG1), U2.3 (EN)
PG_2: J2.10, Q1.1 (G), R12.2, U1.15 (PG2)
U1_temp: J2.12, U1.13 (TEMP)
VCC_REG: C6.1, JP1.3 (B), U1.25 (VCC), U1.27 (VC1)

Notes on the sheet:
Main Power IN: 24V / 90W nom.
GND = Burst Mode Open = forced continuous mode VCC =spread spectrum modulation
fsw=2MHz
Power Levels:
parallel Startup
Automatic Supply Switch-over (pref. to ext.)
